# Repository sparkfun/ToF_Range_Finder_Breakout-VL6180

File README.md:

SparkFun ToF Range Finder Breakout - VL6180
===========================================

[*SparkFun ToF Range Finder Breakout - VL6180 (SEN-12784)*](https://www.sparkfun.com/products/12784)

This is a breakout board for the VL6180 Baby Bear time of flight range finder.
The VL6180 is actually a 3-in-1 package that combines an IR emitter, a range sensor, and an ambient light sensor together for you to easily use. 

Repository Contents
-------------------
* **/Hardware** - All Eagle design files (.brd, .sch)
* **/Libraries** - All Arduino libraries and board examples
* **/Production** - Test bed files and production panel files

Documentation
--------------
* **[Library](https://github.com/sparkfun/SparkFun_ToF_Range_Finder-VL6180_Arduino_Library)** - Arduino  library for the VL6180.
* **[Hookup Guide](https://learn.sparkfun.com/tutorials/vl6180-hookup-guide)** - Basic hookup guide for the VL6180.
* **[SparkFun Fritzing repo](https://github.com/sparkfun/Fritzing_Parts)** - Fritzing diagrams for SparkFun products.
* **[SparkFun 3D Model repo](https://github.com/sparkfun/3D_Models)** - 3D models of SparkFun products. 

License Information
-------------------
This product is _**open source**_! 

The **hardware** is released under [Creative Commons ShareAlike 4.0 International](https://creativecommons.org/licenses/by-sa/4.0/).

The **code** is beerware; if you see me (or any other SparkFun employee) at the local, and you've found our code helpful, please buy us a round!

Please use, reuse, and modify these files as you see fit. Please maintain attribution to SparkFun Electronics and release anything derivative under the same license.

Distributed as-is; no warranty is given.

- Your friends at SparkFun.

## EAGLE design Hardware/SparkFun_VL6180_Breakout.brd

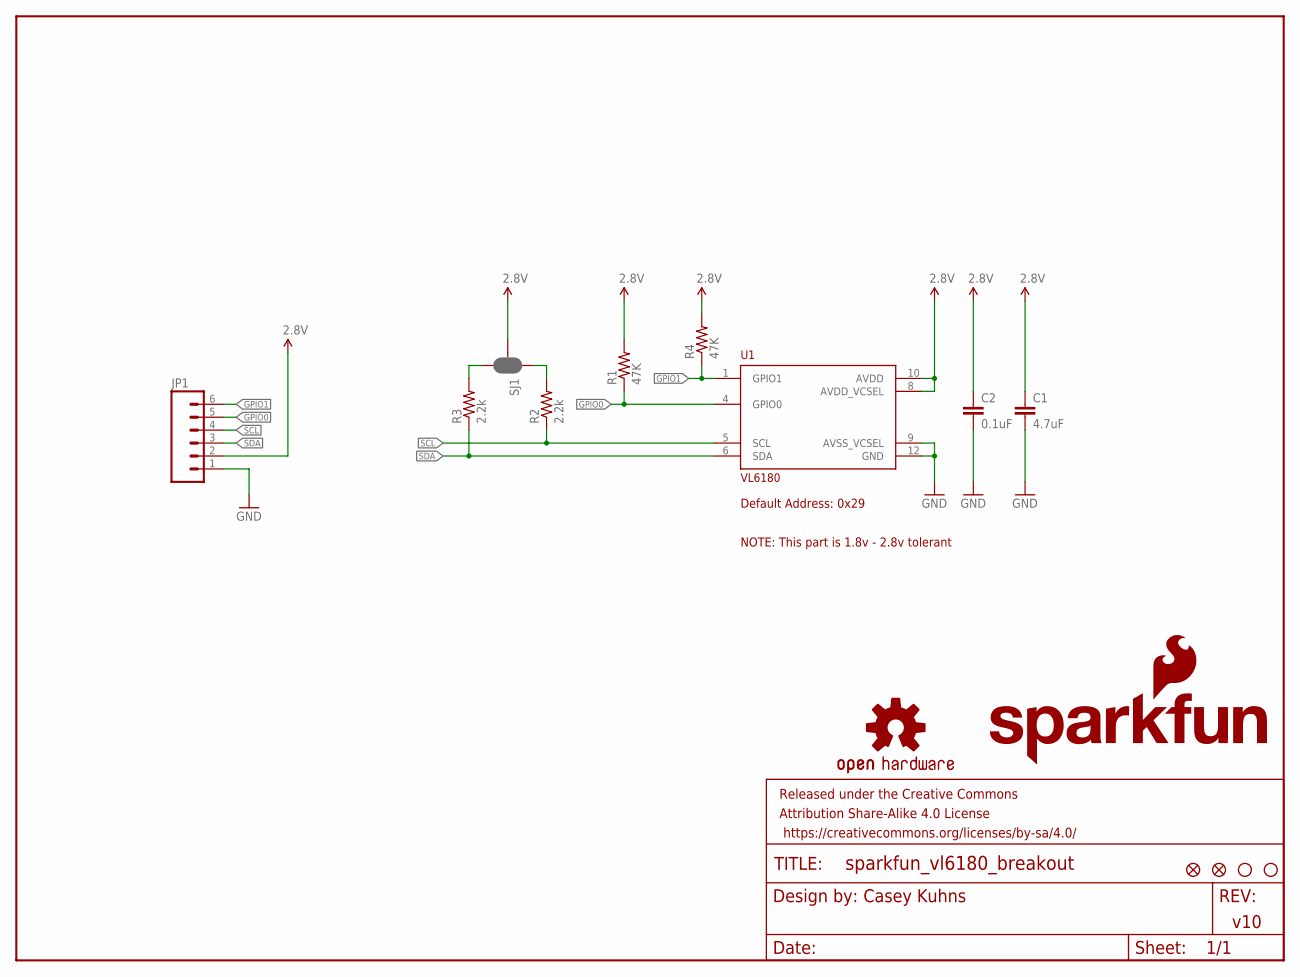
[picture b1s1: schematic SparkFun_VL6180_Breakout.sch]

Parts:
C1: 4.7uF; 0603-CAP
C2: 0.1uF; 0603-CAP
FID1, FID2: FIDUCIAL1X2; FIDUCIAL-1X2
FRAME1: FRAME-LETTER; CREATIVE_COMMONS
JP1: M06SIP; 1X06
LOGO1: SFE_LOGO_NAME_FLAME.1_INCH; SFE_LOGO_NAME_FLAME_.1
LOGO2: OSHW-LOGOS; OSHW-LOGO-S
R1, R4: 47K; 0603-RES
R2, R3: 2.2k; 0603-RES
SJ1: JUMPER-PAD-3-NC_BY_PASTE; PAD-JUMPER-3-NC_BY_PASTE_YES_SILK_FULL_BOX
STANDOFF1, STANDOFF2: STAND-OFF
U1: VL6180

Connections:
2.8V: C1.1, C2.1, JP1.2, R1.2, R4.2, SJ1.2, U1.8 (AVDD_VCSEL), U1.10 (AVDD)
GND: C1.2, C2.2, JP1.1, U1.9 (AVSS_VCSEL), U1.12 (GND)
GPIO0: JP1.5, R1.1, U1.4 (GPIO0)
GPIO1: JP1.6, R4.1, U1.1 (GPIO1)
unnamed: R2.2, SJ1.1
unnamed: R3.2, SJ1.3
SCL: JP1.4, R2.1, U1.5 (SCL)
SDA: JP1.3, R3.1, U1.6 (SDA)

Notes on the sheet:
Casey Kuhns
v10
Default Address: 0x29
NOTE: This part is 1.8v - 2.8v tolerant

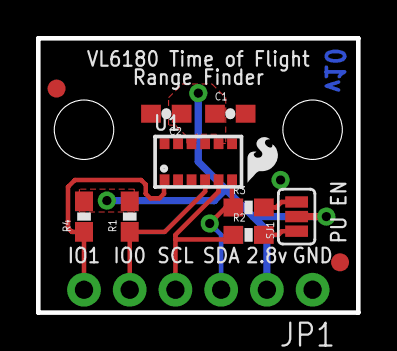
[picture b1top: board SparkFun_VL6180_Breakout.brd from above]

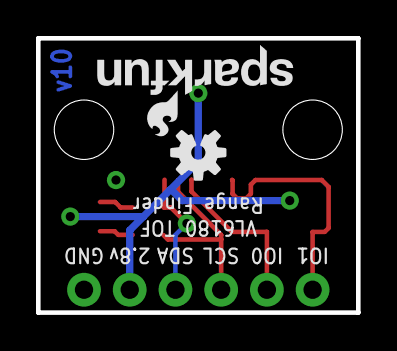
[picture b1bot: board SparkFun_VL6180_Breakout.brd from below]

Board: 2 copper layers, 17.8 x 15.2 mm, 17 parts (2 on the bottom side), 8 nets.

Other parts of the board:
U$2: SFE_LOGO_FLAME_.1

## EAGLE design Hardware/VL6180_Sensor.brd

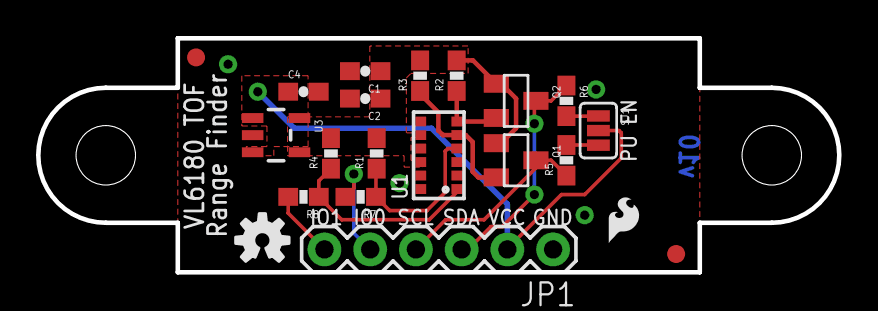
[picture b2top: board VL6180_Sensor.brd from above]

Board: 2 copper layers, 44.5 x 13.0 mm, 25 parts (1 on the bottom side), 13 nets.

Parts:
C1: 4.7uF; 0603-CAP
C2, C4: 0.1uF; 0603-CAP
FID1, FID2: FIDUCIAL1X2; FIDUCIAL-1X2
FRAME1: FRAME-LETTER; CREATIVE_COMMONS
JP1: 1X06
LOGO1: SFE_LOGO_NAME_FLAME.1_INCH; SFE_LOGO_NAME_FLAME_.1
LOGO2: OSHW-LOGOS; OSHW-LOGO-S
Q1, Q2: BSS138; SOT23
R1, R4: 47k; 0603-RES
R2, R3, R5, R6: 2.2k; 0603-RES
R7, R8: 10k; 0603-RES
SJ1: PAD-JUMPER-3-NC_BY_PASTE_YES_SILK_FULL_BOX
STANDOFF1, STANDOFF2: STAND-OFF
U1: VL6180
U3: MIC5219 3.3V; SOT23-5
U$2: SFE_LOGO_FLAME_.1

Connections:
2.8V: C1.1, C2.1, Q1.1, Q2.1, R1.2, R2.2, R3.2, R4.2, U1.8, U1.10, U3.5
GND: C1.2, C2.2, C4.2, JP1.1, U1.9, U1.12, U3.2
GPIO0: JP1.5, R7.2
GPIO1: JP1.6, R8.2
unnamed: R6.2, SJ1.1
unnamed: R5.2, SJ1.3
unnamed: R1.1, R7.1, U1.4
unnamed: R4.1, R8.1, U1.1
SCL: JP1.4, Q1.3, R5.1
SCL_LV: Q1.2, R3.1, U1.5
SDA: JP1.3, Q2.3, R6.1
SDA_LV: Q2.2, R2.1, U1.6
VCC: C4.1, JP1.2, SJ1.2, U3.1, U3.3

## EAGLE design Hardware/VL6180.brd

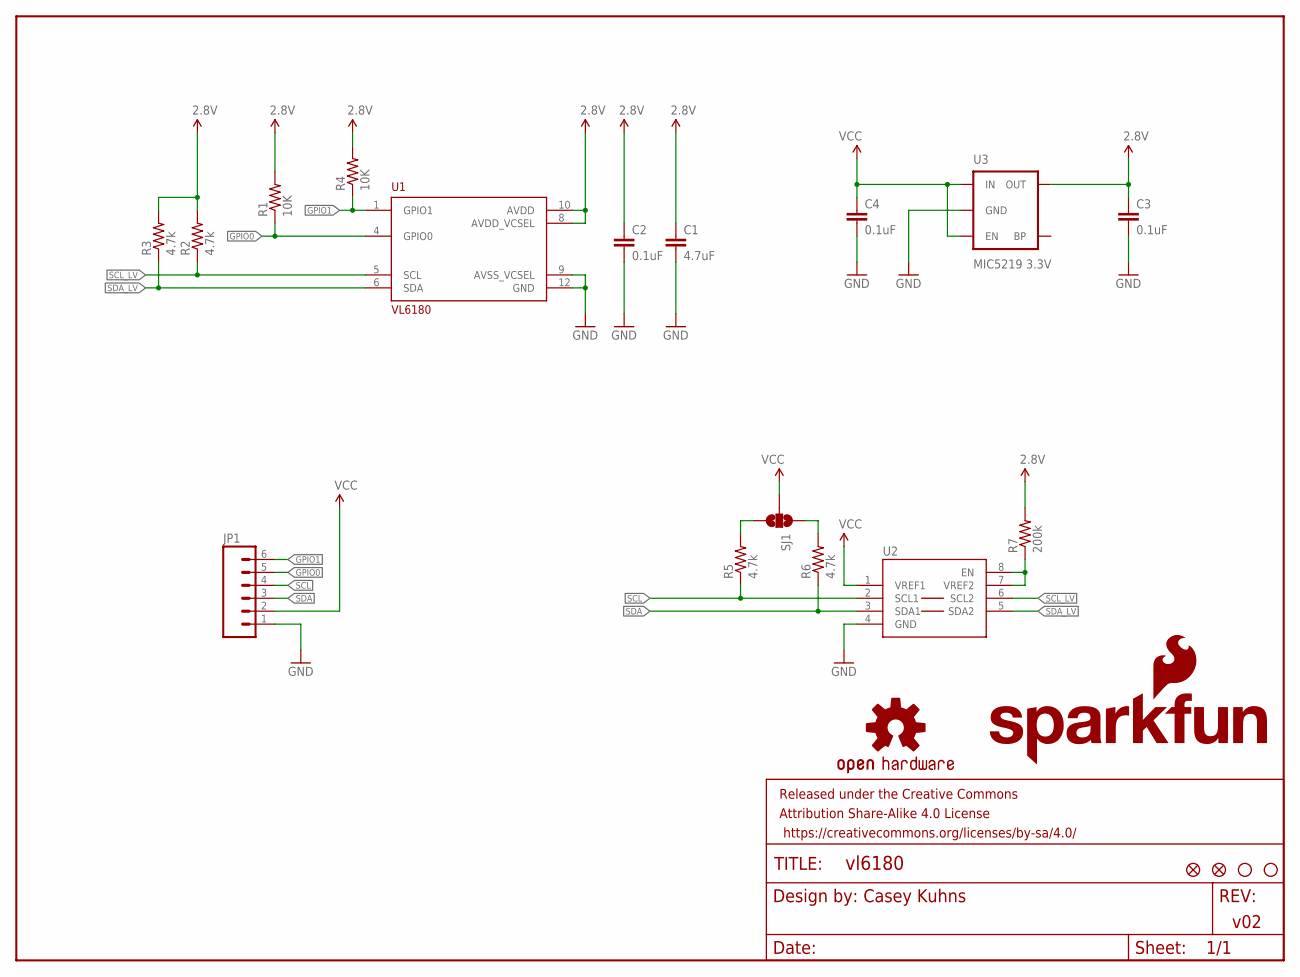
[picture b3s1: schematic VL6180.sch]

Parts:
C1: 4.7uF; 0603-CAP
C2, C3, C4: 0.1uF; 0603-CAP
FID1, FID2: FIDUCIAL1X2; FIDUCIAL-1X2
FRAME1: FRAME-LETTER; CREATIVE_COMMONS
JP1: M06SIP; 1X06
LOGO1: SFE_LOGO_NAME_FLAME.1_INCH; SFE_LOGO_NAME_FLAME_.1
LOGO2: OSHW-LOGOS; OSHW-LOGO-S
R1, R4: 10K; 0603-RES
R2, R3, R5, R6: 4.7k; 0603
R7: 200k; 0603-RES
SJ1: SOLDERJUMPER_2WAYPASTE1&2&3; SJ_3_PASTE1&2&3
STANDOFF1, STANDOFF2: STAND-OFF
U1: VL6180
U2: PCA9306; PSOP-8
U3: MIC5219 3.3V; SOT23-5

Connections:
2.8V: C1.1, C2.1, C3.1, R1.2, R2.2, R3.2, R4.2, R7.2, U1.8 (AVDD_VCSEL), U1.10 (AVDD), U3.5 (OUT)
GND: C1.2, C2.2, C3.2, C4.2, JP1.1, U1.9 (AVSS_VCSEL), U1.12 (GND), U2.4 (GND), U3.2 (GND)
GPIO0: JP1.5, R1.1, U1.4 (GPIO0)
GPIO1: JP1.6, R4.1, U1.1 (GPIO1)
unnamed: R7.1, U2.7 (VREF2), U2.8 (EN)
unnamed: R6.2, SJ1.1
unnamed: R5.2, SJ1.3
SCL: JP1.4, R5.1, U2.2 (SCL1)
SCL_LV: R2.1, U1.5 (SCL), U2.6 (SCL2)
SDA: JP1.3, R6.1, U2.3 (SDA1)
SDA_LV: R3.1, U1.6 (SDA), U2.5 (SDA2)
VCC: C4.1, JP1.2, SJ1.2, U2.1 (VREF1), U3.1 (IN), U3.3 (EN)

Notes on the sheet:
Casey Kuhns
v02

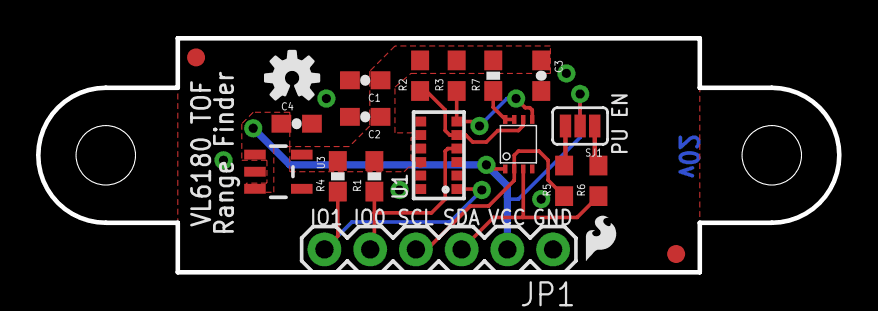
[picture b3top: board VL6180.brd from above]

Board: 2 copper layers, 44.5 x 13.0 mm, 24 parts (1 on the bottom side), 12 nets.

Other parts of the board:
U$2: SFE_LOGO_FLAME_.1

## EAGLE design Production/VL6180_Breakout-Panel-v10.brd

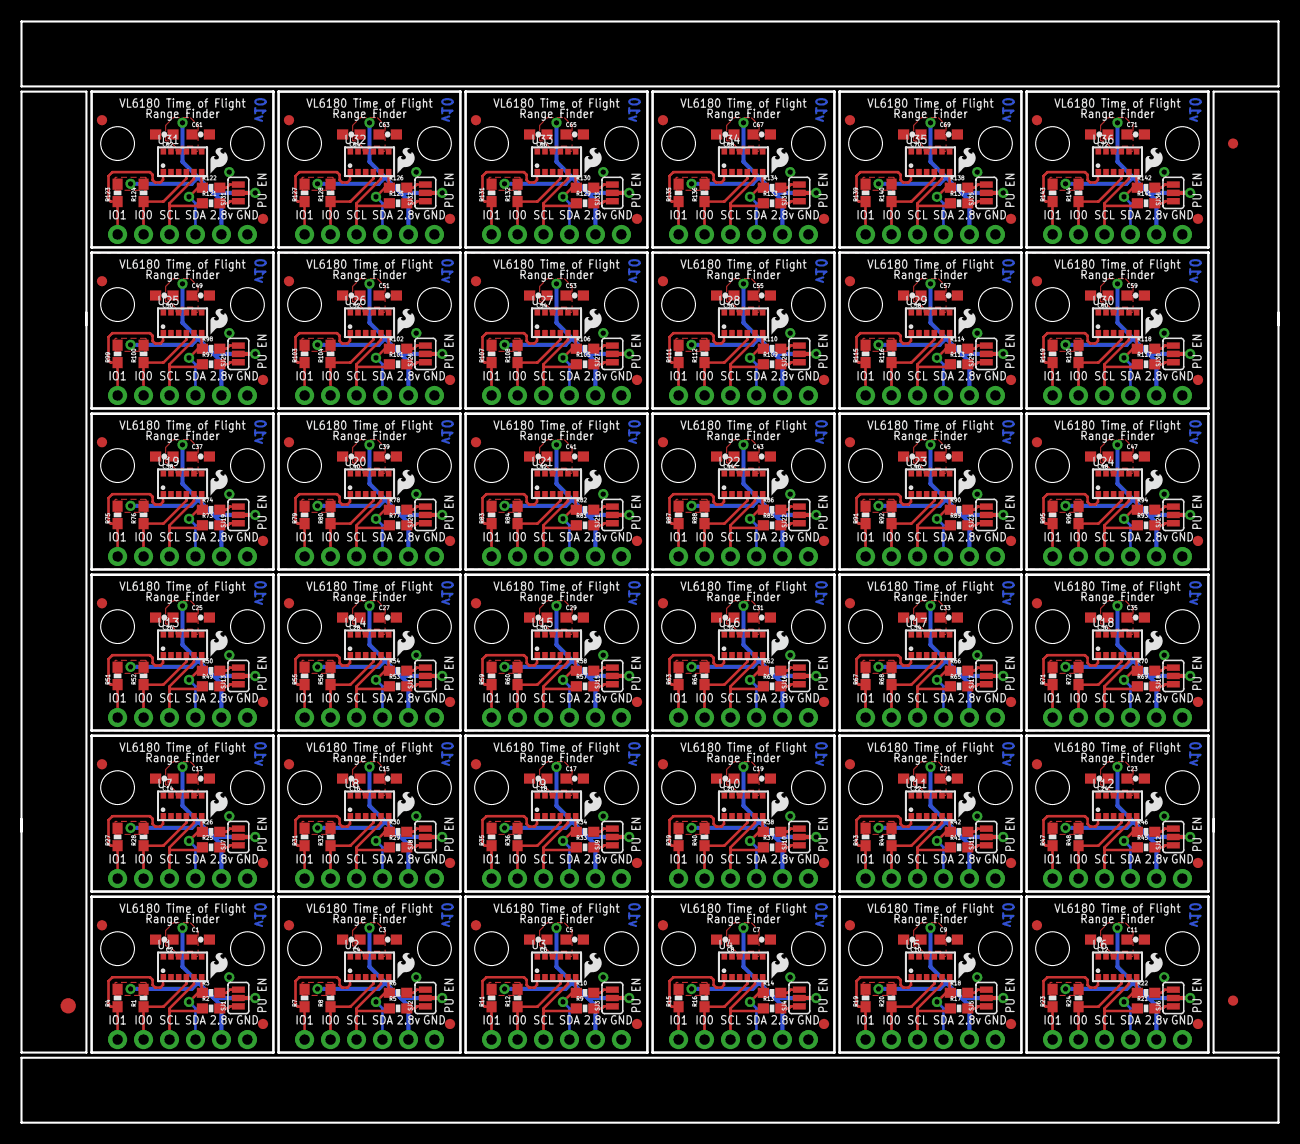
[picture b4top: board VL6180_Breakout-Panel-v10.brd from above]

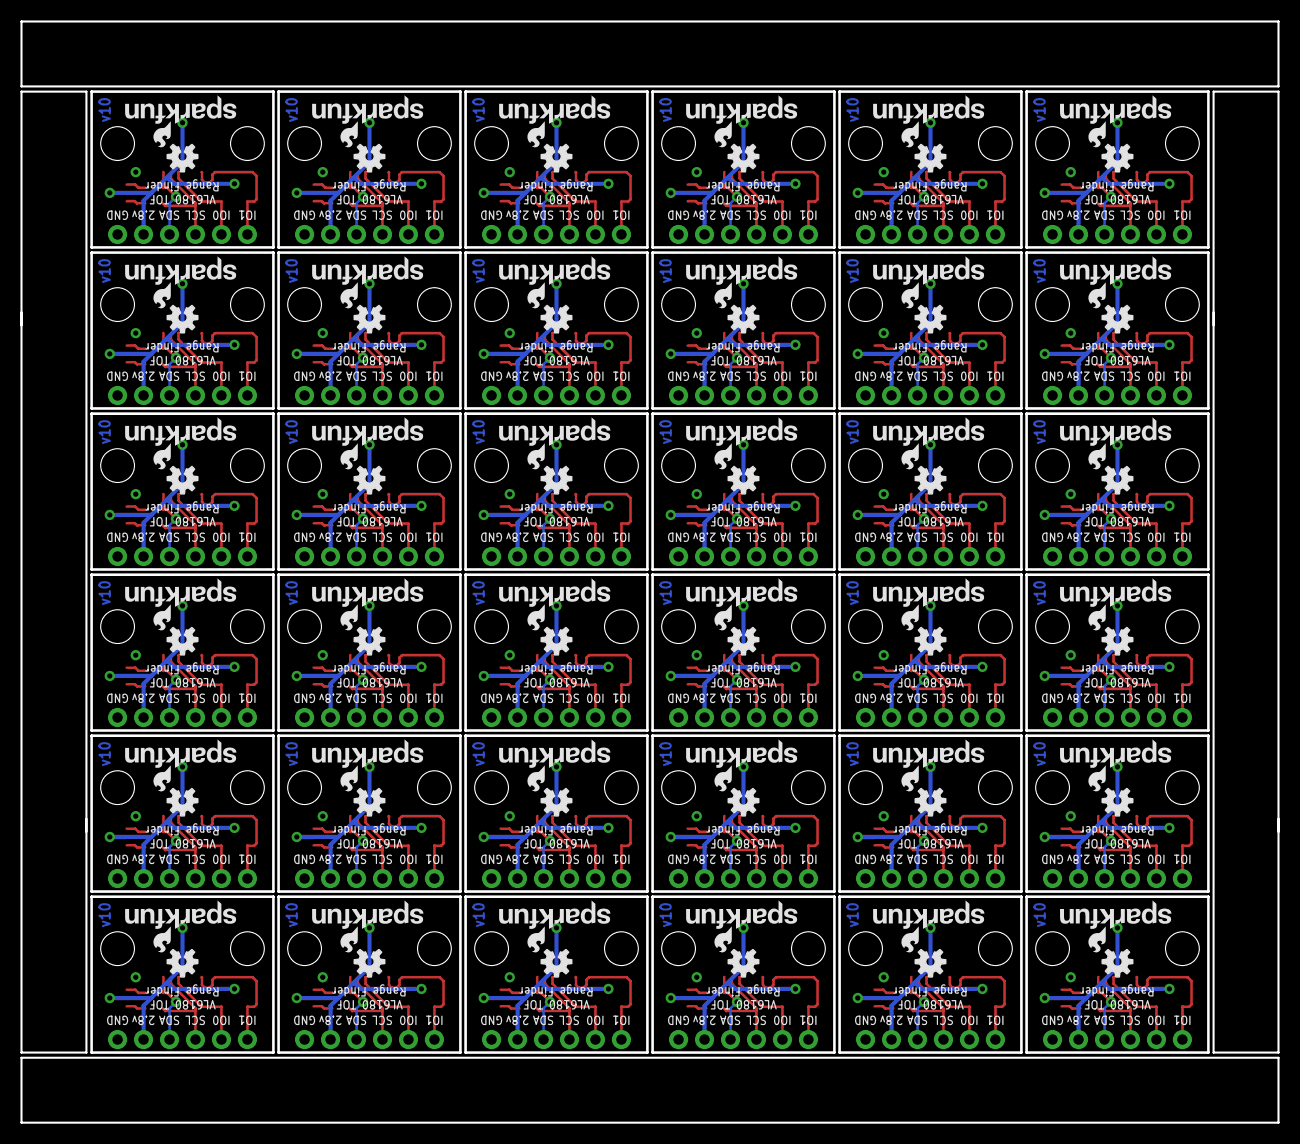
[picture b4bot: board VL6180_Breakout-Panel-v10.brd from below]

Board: 2 copper layers, 122.9 x 107.6 mm, 579 parts (72 on the bottom side), 288 nets.

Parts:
C1, C3, C5, C7, C9, C11, C13, C15, C17, C19, C21, C23, C25, C27, C29, C31, C33, C35, C37, C39, C41, C43, C45, C47, C49, C51, C53, C55, C57, C59, C61, C63, C65, C67, C69, C71: 4.7uF; 0603-CAP
C2, C4, C6, C8, C10, C12, C14, C16, C18, C20, C22, C24, C26, C28, C30, C32, C34, C36, C38, C40, C42, C44, C46, C48, C50, C52, C54, C56, C58, C60, C62, C64, C66, C68, C70, C72: 0.1uF; 0603-CAP
E$1: FIDUCIAL-1.5X3
E$4, E$6: FIDUCIAL-1X2
FID1, FID2, FID3, FID4, FID5, FID6, FID7, FID8, FID9, FID10, FID11, FID12, FID13, FID14, FID15, FID16, FID17, FID18, FID19, FID20, FID21, FID22, FID23, FID24, FID25, FID26, FID27, FID28, FID29, FID30, FID31, FID32, FID33, FID34, FID35, FID36, FID37, FID38, FID39, FID40, FID41, FID42, FID43, FID44, FID45, FID46, FID47, FID48, FID49, FID50, FID51, FID52, FID53, FID54, FID55, FID56, FID57, FID58, FID59, FID60, FID61, FID62, FID63, FID64, FID65, FID66, FID67, FID68, FID69, FID70, FID71, FID72: FIDUCIAL1X2; FIDUCIAL-1X2
JP1, JP2, JP3, JP4, JP5, JP6, JP7, JP8, JP9, JP10, JP11, JP12, JP13, JP14, JP15, JP16, JP17, JP18, JP19, JP20, JP21, JP22, JP23, JP24, JP25, JP26, JP27, JP28, JP29, JP30, JP31, JP32, JP33, JP34, JP35, JP36: 1X06
LOGO1, LOGO3, LOGO5, LOGO7, LOGO9, LOGO11, LOGO13, LOGO15, LOGO17, LOGO19, LOGO21, LOGO23, LOGO25, LOGO27, LOGO29, LOGO31, LOGO33, LOGO35, LOGO37, LOGO39, LOGO41, LOGO43, LOGO45, LOGO47, LOGO49, LOGO51, LOGO53, LOGO55, LOGO57, LOGO59, LOGO61, LOGO63, LOGO65, LOGO67, LOGO69, LOGO71: SFE_LOGO_NAME_FLAME.1_INCH; SFE_LOGO_NAME_FLAME_.1
LOGO2, LOGO4, LOGO6, LOGO8, LOGO10, LOGO12, LOGO14, LOGO16, LOGO18, LOGO20, LOGO22, LOGO24, LOGO26, LOGO28, LOGO30, LOGO32, LOGO34, LOGO36, LOGO38, LOGO40, LOGO42, LOGO44, LOGO46, LOGO48, LOGO50, LOGO52, LOGO54, LOGO56, LOGO58, LOGO60, LOGO62, LOGO64, LOGO66, LOGO68, LOGO70, LOGO72: OSHW-LOGOS; OSHW-LOGO-S
R1, R4, R7, R8, R11, R12, R15, R16, R19, R20, R23, R24, R27, R28, R31, R32, R35, R36, R39, R40, R43, R44, R47, R48, R51, R52, R55, R56, R59, R60, R63, R64, R67, R68, R71, R72, R75, R76, R79, R80, R83, R84, R87, R88, R91, R92, R95, R96, R99, R100, R103, R104, R107, R108, R111, R112, R115, R116, R119, R120, R123, R124, R127, R128, R131, R132, R135, R136, R139, R140, R143, R144: 47K; 0603-RES
R2, R3, R5, R6, R9, R10, R13, R14, R17, R18, R21, R22, R25, R26, R29, R30, R33, R34, R37, R38, R41, R42, R45, R46, R49, R50, R53, R54, R57, R58, R61, R62, R65, R66, R69, R70, R73, R74, R77, R78, R81, R82, R85, R86, R89, R90, R93, R94, R97, R98, R101, R102, R105, R106, R109, R110, R113, R114, R117, R118, R121, R122, R125, R126, R129, R130, R133, R134, R137, R138, R141, R142: 2.2k; 0603-RES
SJ1, SJ2, SJ3, SJ4, SJ5, SJ6, SJ7, SJ8, SJ9, SJ10, SJ11, SJ12, SJ13, SJ14, SJ15, SJ16, SJ17, SJ18, SJ19, SJ20, SJ21, SJ22, SJ23, SJ24, SJ25, SJ26, SJ27, SJ28, SJ29, SJ30, SJ31, SJ32, SJ33, SJ34, SJ35, SJ36: PAD-JUMPER-3-NC_BY_PASTE_YES_SILK_FULL_BOX
STANDOFF1, STANDOFF2, STANDOFF3, STANDOFF4, STANDOFF5, STANDOFF6, STANDOFF7, STANDOFF8, STANDOFF9, STANDOFF10, STANDOFF11, STANDOFF12, STANDOFF13, STANDOFF14, STANDOFF15, STANDOFF16, STANDOFF17, STANDOFF18, STANDOFF19, STANDOFF20, STANDOFF21, STANDOFF22, STANDOFF23, STANDOFF24, STANDOFF25, STANDOFF26, STANDOFF27, STANDOFF28, STANDOFF29, STANDOFF30, STANDOFF31, STANDOFF32, STANDOFF33, STANDOFF34, STANDOFF35, STANDOFF36, STANDOFF37, STANDOFF38, STANDOFF39, STANDOFF40, STANDOFF41, STANDOFF42, STANDOFF43, STANDOFF44, STANDOFF45, STANDOFF46, STANDOFF47, STANDOFF48, STANDOFF49, STANDOFF50, STANDOFF51, STANDOFF52, STANDOFF53, STANDOFF54, STANDOFF55, STANDOFF56, STANDOFF57, STANDOFF58, STANDOFF59, STANDOFF60, STANDOFF61, STANDOFF62, STANDOFF63, STANDOFF64, STANDOFF65, STANDOFF66, STANDOFF67, STANDOFF68, STANDOFF69, STANDOFF70, STANDOFF71, STANDOFF72: STAND-OFF
U1, U2, U3, U4, U5, U6, U7, U8, U9, U10, U11, U12, U13, U14, U15, U16, U17, U18, U19, U20, U21, U22, U23, U24, U25, U26, U27, U28, U29, U30, U31, U32, U33, U34, U35, U36: VL6180
U$1, U$2, U$3, U$4, U$5, U$6, U$7, U$8, U$9, U$10, U$11, U$12, U$13, U$14, U$15, U$16, U$17, U$18, U$19, U$20, U$21, U$22, U$23, U$24, U$25, U$26, U$27, U$28, U$29, U$30, U$31, U$32, U$33, U$34, U$35, U$36: SFE_LOGO_FLAME_.1

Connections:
2.8V: C1.1, C2.1, JP1.2, R1.2, R4.2, SJ1.2, U1.8, U1.10
2.8V1: C3.1, C4.1, JP2.2, R7.2, R8.2, SJ2.2, U2.8, U2.10
2.8V2: C5.1, C6.1, JP3.2, R11.2, R12.2, SJ3.2, U3.8, U3.10
2.8V3: C7.1, C8.1, JP4.2, R15.2, R16.2, SJ4.2, U4.8, U4.10
2.8V4: C9.1, C10.1, JP5.2, R19.2, R20.2, SJ5.2, U5.8, U5.10
2.8V5: C11.1, C12.1, JP6.2, R23.2, R24.2, SJ6.2, U6.8, U6.10
2.8V6: C13.1, C14.1, JP7.2, R27.2, R28.2, SJ7.2, U7.8, U7.10
2.8V7: C15.1, C16.1, JP8.2, R31.2, R32.2, SJ8.2, U8.8, U8.10
2.8V8: C17.1, C18.1, JP9.2, R35.2, R36.2, SJ9.2, U9.8, U9.10
2.8V9: C19.1, C20.1, JP10.2, R39.2, R40.2, SJ10.2, U10.8, U10.10
2.8V10: C21.1, C22.1, JP11.2, R43.2, R44.2, SJ11.2, U11.8, U11.10
2.8V11: C23.1, C24.1, JP12.2, R47.2, R48.2, SJ12.2, U12.8, U12.10
2.8V12: C25.1, C26.1, JP13.2, R51.2, R52.2, SJ13.2, U13.8, U13.10
2.8V13: C27.1, C28.1, JP14.2, R55.2, R56.2, SJ14.2, U14.8, U14.10
2.8V14: C29.1, C30.1, JP15.2, R59.2, R60.2, SJ15.2, U15.8, U15.10
2.8V15: C31.1, C32.1, JP16.2, R63.2, R64.2, SJ16.2, U16.8, U16.10
2.8V16: C33.1, C34.1, JP17.2, R67.2, R68.2, SJ17.2, U17.8, U17.10
2.8V17: C35.1, C36.1, JP18.2, R71.2, R72.2, SJ18.2, U18.8, U18.10
2.8V18: C37.1, C38.1, JP19.2, R75.2, R76.2, SJ19.2, U19.8, U19.10
2.8V19: C39.1, C40.1, JP20.2, R79.2, R80.2, SJ20.2, U20.8, U20.10
2.8V20: C41.1, C42.1, JP21.2, R83.2, R84.2, SJ21.2, U21.8, U21.10
2.8V21: C43.1, C44.1, JP22.2, R87.2, R88.2, SJ22.2, U22.8, U22.10
2.8V22: C45.1, C46.1, JP23.2, R91.2, R92.2, SJ23.2, U23.8, U23.10
2.8V23: C47.1, C48.1, JP24.2, R95.2, R96.2, SJ24.2, U24.8, U24.10
2.8V24: C49.1, C50.1, JP25.2, R99.2, R100.2, SJ25.2, U25.8, U25.10
2.8V25: C51.1, C52.1, JP26.2, R103.2, R104.2, SJ26.2, U26.8, U26.10
2.8V26: C53.1, C54.1, JP27.2, R107.2, R108.2, SJ27.2, U27.8, U27.10
2.8V27: C55.1, C56.1, JP28.2, R111.2, R112.2, SJ28.2, U28.8, U28.10
2.8V28: C57.1, C58.1, JP29.2, R115.2, R116.2, SJ29.2, U29.8, U29.10
2.8V29: C59.1, C60.1, JP30.2, R119.2, R120.2, SJ30.2, U30.8, U30.10
2.8V30: C61.1, C62.1, JP31.2, R123.2, R124.2, SJ31.2, U31.8, U31.10
2.8V31: C63.1, C64.1, JP32.2, R127.2, R128.2, SJ32.2, U32.8, U32.10
2.8V32: C65.1, C66.1, JP33.2, R131.2, R132.2, SJ33.2, U33.8, U33.10
2.8V33: C67.1, C68.1, JP34.2, R135.2, R136.2, SJ34.2, U34.8, U34.10
2.8V34: C69.1, C70.1, JP35.2, R139.2, R140.2, SJ35.2, U35.8, U35.10
2.8V35: C71.1, C72.1, JP36.2, R143.2, R144.2, SJ36.2, U36.8, U36.10
GND: C1.2, C2.2, JP1.1, U1.9, U1.12
GND1: C3.2, C4.2, JP2.1, U2.9, U2.12
GND2: C5.2, C6.2, JP3.1, U3.9, U3.12
GND3: C7.2, C8.2, JP4.1, U4.9, U4.12
GND4: C9.2, C10.2, JP5.1, U5.9, U5.12
GND5: C11.2, C12.2, JP6.1, U6.9, U6.12
GND6: C13.2, C14.2, JP7.1, U7.9, U7.12
GND7: C15.2, C16.2, JP8.1, U8.9, U8.12
GND8: C17.2, C18.2, JP9.1, U9.9, U9.12
GND9: C19.2, C20.2, JP10.1, U10.9, U10.12
GND10: C21.2, C22.2, JP11.1, U11.9, U11.12
GND11: C23.2, C24.2, JP12.1, U12.9, U12.12
GND12: C25.2, C26.2, JP13.1, U13.9, U13.12
GND13: C27.2, C28.2, JP14.1, U14.9, U14.12
GND14: C29.2, C30.2, JP15.1, U15.9, U15.12
GND15: C31.2, C32.2, JP16.1, U16.9, U16.12
GND16: C33.2, C34.2, JP17.1, U17.9, U17.12
GND17: C35.2, C36.2, JP18.1, U18.9, U18.12
GND18: C37.2, C38.2, JP19.1, U19.9, U19.12
GND19: C39.2, C40.2, JP20.1, U20.9, U20.12
GND20: C41.2, C42.2, JP21.1, U21.9, U21.12
GND21: C43.2, C44.2, JP22.1, U22.9, U22.12
GND22: C45.2, C46.2, JP23.1, U23.9, U23.12
GND23: C47.2, C48.2, JP24.1, U24.9, U24.12
GND24: C49.2, C50.2, JP25.1, U25.9, U25.12
GND25: C51.2, C52.2, JP26.1, U26.9, U26.12
GND26: C53.2, C54.2, JP27.1, U27.9, U27.12
GND27: C55.2, C56.2, JP28.1, U28.9, U28.12
GND28: C57.2, C58.2, JP29.1, U29.9, U29.12
GND29: C59.2, C60.2, JP30.1, U30.9, U30.12
GND30: C61.2, C62.2, JP31.1, U31.9, U31.12
GND31: C63.2, C64.2, JP32.1, U32.9, U32.12
GND32: C65.2, C66.2, JP33.1, U33.9, U33.12
GND33: C67.2, C68.2, JP34.1, U34.9, U34.12
GND34: C69.2, C70.2, JP35.1, U35.9, U35.12
GND35: C71.2, C72.2, JP36.1, U36.9, U36.12
GPIO0: JP1.5, R1.1, U1.4
GPIO1: JP1.6, R4.1, U1.1
GPIO2: JP2.5, R8.1, U2.4
GPIO3: JP2.6, R7.1, U2.1
GPIO4: JP3.5, R12.1, U3.4
GPIO5: JP3.6, R11.1, U3.1
GPIO6: JP4.5, R16.1, U4.4
GPIO7: JP4.6, R15.1, U4.1
GPIO8: JP5.5, R20.1, U5.4
GPIO9: JP5.6, R19.1, U5.1
GPIO10: JP6.5, R24.1, U6.4
GPIO11: JP6.6, R23.1, U6.1
GPIO12: JP7.5, R28.1, U7.4
GPIO13: JP7.6, R27.1, U7.1
GPIO14: JP8.5, R32.1, U8.4
GPIO15: JP8.6, R31.1, U8.1
GPIO16: JP9.5, R36.1, U9.4
GPIO17: JP9.6, R35.1, U9.1
GPIO18: JP10.5, R40.1, U10.4
GPIO19: JP10.6, R39.1, U10.1
GPIO20: JP11.5, R44.1, U11.4
GPIO21: JP11.6, R43.1, U11.1
GPIO22: JP12.5, R48.1, U12.4
GPIO23: JP12.6, R47.1, U12.1
GPIO24: JP13.5, R52.1, U13.4
GPIO25: JP13.6, R51.1, U13.1
GPIO26: JP14.5, R56.1, U14.4
GPIO27: JP14.6, R55.1, U14.1
GPIO28: JP15.5, R60.1, U15.4
GPIO29: JP15.6, R59.1, U15.1
GPIO30: JP16.5, R64.1, U16.4
GPIO31: JP16.6, R63.1, U16.1
GPIO32: JP17.5, R68.1, U17.4
GPIO33: JP17.6, R67.1, U17.1
GPIO34: JP18.5, R72.1, U18.4
GPIO35: JP18.6, R71.1, U18.1
GPIO36: JP19.5, R76.1, U19.4
GPIO37: JP19.6, R75.1, U19.1
GPIO38: JP20.5, R80.1, U20.4
GPIO39: JP20.6, R79.1, U20.1
GPIO40: JP21.5, R84.1, U21.4
GPIO41: JP21.6, R83.1, U21.1
GPIO42: JP22.5, R88.1, U22.4
GPIO43: JP22.6, R87.1, U22.1
GPIO44: JP23.5, R92.1, U23.4
GPIO45: JP23.6, R91.1, U23.1
GPIO46: JP24.5, R96.1, U24.4
GPIO47: JP24.6, R95.1, U24.1
GPIO48: JP25.5, R100.1, U25.4
GPIO49: JP25.6, R99.1, U25.1
GPIO50: JP26.5, R104.1, U26.4
GPIO51: JP26.6, R103.1, U26.1
GPIO52: JP27.5, R108.1, U27.4
GPIO53: JP27.6, R107.1, U27.1
GPIO54: JP28.5, R112.1, U28.4
GPIO55: JP28.6, R111.1, U28.1
GPIO56: JP29.5, R116.1, U29.4
GPIO57: JP29.6, R115.1, U29.1
GPIO58: JP30.5, R120.1, U30.4
GPIO59: JP30.6, R119.1, U30.1
GPIO60: JP31.5, R124.1, U31.4
GPIO61: JP31.6, R123.1, U31.1
GPIO62: JP32.5, R128.1, U32.4
GPIO63: JP32.6, R127.1, U32.1
GPIO64: JP33.5, R132.1, U33.4
GPIO65: JP33.6, R131.1, U33.1
GPIO66: JP34.5, R136.1, U34.4
GPIO67: JP34.6, R135.1, U34.1
GPIO68: JP35.5, R140.1, U35.4
GPIO69: JP35.6, R139.1, U35.1
GPIO70: JP36.5, R144.1, U36.4
GPIO71: JP36.6, R143.1, U36.1
unnamed: R2.2, SJ1.1
unnamed: R3.2, SJ1.3
unnamed: R5.2, SJ2.1
unnamed: R6.2, SJ2.3
unnamed: R9.2, SJ3.1
unnamed: R10.2, SJ3.3
unnamed: R13.2, SJ4.1
unnamed: R14.2, SJ4.3
unnamed: R17.2, SJ5.1
unnamed: R18.2, SJ5.3
unnamed: R21.2, SJ6.1
unnamed: R22.2, SJ6.3
unnamed: R25.2, SJ7.1
unnamed: R26.2, SJ7.3
unnamed: R29.2, SJ8.1
unnamed: R30.2, SJ8.3
unnamed: R33.2, SJ9.1
unnamed: R34.2, SJ9.3
unnamed: R37.2, SJ10.1
unnamed: R38.2, SJ10.3
unnamed: R41.2, SJ11.1
unnamed: R42.2, SJ11.3
unnamed: R45.2, SJ12.1
unnamed: R46.2, SJ12.3
unnamed: R49.2, SJ13.1
unnamed: R50.2, SJ13.3
unnamed: R53.2, SJ14.1
unnamed: R54.2, SJ14.3
unnamed: R57.2, SJ15.1
unnamed: R58.2, SJ15.3
unnamed: R61.2, SJ16.1
unnamed: R62.2, SJ16.3
unnamed: R65.2, SJ17.1
unnamed: R66.2, SJ17.3
unnamed: R69.2, SJ18.1
unnamed: R70.2, SJ18.3
unnamed: R73.2, SJ19.1
unnamed: R74.2, SJ19.3
unnamed: R77.2, SJ20.1
unnamed: R78.2, SJ20.3
unnamed: R81.2, SJ21.1
unnamed: R82.2, SJ21.3
unnamed: R85.2, SJ22.1
unnamed: R86.2, SJ22.3
unnamed: R89.2, SJ23.1
unnamed: R90.2, SJ23.3
unnamed: R93.2, SJ24.1
unnamed: R94.2, SJ24.3
unnamed: R97.2, SJ25.1
unnamed: R98.2, SJ25.3
unnamed: R101.2, SJ26.1
unnamed: R102.2, SJ26.3
unnamed: R105.2, SJ27.1
unnamed: R106.2, SJ27.3
unnamed: R109.2, SJ28.1
unnamed: R110.2, SJ28.3
unnamed: R113.2, SJ29.1
unnamed: R114.2, SJ29.3
unnamed: R117.2, SJ30.1
unnamed: R118.2, SJ30.3
unnamed: R121.2, SJ31.1
unnamed: R122.2, SJ31.3
unnamed: R125.2, SJ32.1
unnamed: R126.2, SJ32.3
unnamed: R129.2, SJ33.1
unnamed: R130.2, SJ33.3
unnamed: R133.2, SJ34.1
unnamed: R134.2, SJ34.3
unnamed: R137.2, SJ35.1
unnamed: R138.2, SJ35.3
unnamed: R141.2, SJ36.1
unnamed: R142.2, SJ36.3
SCL: JP1.4, R2.1, U1.5
SCL1: JP2.4, R5.1, U2.5
SCL2: JP3.4, R9.1, U3.5
SCL3: JP4.4, R13.1, U4.5
SCL4: JP5.4, R17.1, U5.5
SCL5: JP6.4, R21.1, U6.5
SCL6: JP7.4, R25.1, U7.5
SCL7: JP8.4, R29.1, U8.5
SCL8: JP9.4, R33.1, U9.5
SCL9: JP10.4, R37.1, U10.5
SCL10: JP11.4, R41.1, U11.5
SCL11: JP12.4, R45.1, U12.5
SCL12: JP13.4, R49.1, U13.5
SCL13: JP14.4, R53.1, U14.5
SCL14: JP15.4, R57.1, U15.5
SCL15: JP16.4, R61.1, U16.5
SCL16: JP17.4, R65.1, U17.5
SCL17: JP18.4, R69.1, U18.5
SCL18: JP19.4, R73.1, U19.5
SCL19: JP20.4, R77.1, U20.5
SCL20: JP21.4, R81.1, U21.5
SCL21: JP22.4, R85.1, U22.5
SCL22: JP23.4, R89.1, U23.5
SCL23: JP24.4, R93.1, U24.5
SCL24: JP25.4, R97.1, U25.5
SCL25: JP26.4, R101.1, U26.5
SCL26: JP27.4, R105.1, U27.5
SCL27: JP28.4, R109.1, U28.5
SCL28: JP29.4, R113.1, U29.5
SCL29: JP30.4, R117.1, U30.5
SCL30: JP31.4, R121.1, U31.5
SCL31: JP32.4, R125.1, U32.5
SCL32: JP33.4, R129.1, U33.5
SCL33: JP34.4, R133.1, U34.5
SCL34: JP35.4, R137.1, U35.5
SCL35: JP36.4, R141.1, U36.5
SDA: JP1.3, R3.1, U1.6
SDA1: JP2.3, R6.1, U2.6
SDA2: JP3.3, R10.1, U3.6
SDA3: JP4.3, R14.1, U4.6
SDA4: JP5.3, R18.1, U5.6
SDA5: JP6.3, R22.1, U6.6
SDA6: JP7.3, R26.1, U7.6
SDA7: JP8.3, R30.1, U8.6
SDA8: JP9.3, R34.1, U9.6
SDA9: JP10.3, R38.1, U10.6
SDA10: JP11.3, R42.1, U11.6
SDA11: JP12.3, R46.1, U12.6
SDA12: JP13.3, R50.1, U13.6
SDA13: JP14.3, R54.1, U14.6
SDA14: JP15.3, R58.1, U15.6
SDA15: JP16.3, R62.1, U16.6
SDA16: JP17.3, R66.1, U17.6
SDA17: JP18.3, R70.1, U18.6
SDA18: JP19.3, R74.1, U19.6
SDA19: JP20.3, R78.1, U20.6
SDA20: JP21.3, R82.1, U21.6
SDA21: JP22.3, R86.1, U22.6
SDA22: JP23.3, R90.1, U23.6
SDA23: JP24.3, R94.1, U24.6
SDA24: JP25.3, R98.1, U25.6
SDA25: JP26.3, R102.1, U26.6
SDA26: JP27.3, R106.1, U27.6
SDA27: JP28.3, R110.1, U28.6
SDA28: JP29.3, R114.1, U29.6
SDA29: JP30.3, R118.1, U30.6
SDA30: JP31.3, R122.1, U31.6
SDA31: JP32.3, R126.1, U32.6
SDA32: JP33.3, R130.1, U33.6
SDA33: JP34.3, R134.1, U34.6
SDA34: JP35.3, R138.1, U35.6
SDA35: JP36.3, R142.1, U36.6

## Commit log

2014-02-21 initial commit with initial hardware layout
2014-02-28 Boad Layout finished, looking for review
2014-03-03 finished layout and added simple breakout board layout
2014-03-03 changed VCC label on breakout to 2.8v to re-state 2.8v compatible
2014-03-04 Changed I2C EN to PU EN
2014-03-13 fixed flipped pin problem. 8-9 on the sensor were reversed somehow. All better :)
2014-03-25 added pin 1 designator
2014-05-01 modified: Hardware/VL6180_Breakout.brd modified: Hardware/VL6180_Breakout.sch renamed: Hardware/VL6180.brd -> Hardware/VL6180_Sensor.brd renamed: Hardware/VL6180.sch -> Hardware/VL6180_Sensor.sch
    Removed I2C level shifter and switched to Fet bases solution.
    New solderpaste footprint for VL6180 for improved reflow.
    updated all parts with Sparkle ID's
2014-05-28 changed I2C resistors to 2.2k, added current limiting resistor on GPIO pins.
2014-05-29 moved wire to clear resistor better, re-oriented Silkscreen to match direction of logo.
2014-05-29 created Sensor panel v10
2014-05-29 created breakout panel v10
2014-10-28 started work on Library
2014-10-29 added files to libs
2014-10-29 worked on the class
2014-10-31 work in progress
2015-01-23 worked on Library, currently functioning, building more features
2015-02-10 split repo
2015-02-13 Updating README with product info
2015-05-14 Fixing structure, naming conventions
2015-05-14 Squashed 'Libraries/Arduino/' content from commit dd6cce0
    git-subtree-dir: Libraries/Arduino
    git-subtree-split: dd6cce03c074b9068238a3e29b15535ec5eadf2b

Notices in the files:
parts and their libraries:
SparkFun-Aesthetics: Licensing: CC v3.0 Share-Alike You are welcome to use this library for commercial purposes.
SparkFun-Aesthetics: Released under the Creative Commons Attribution Share-Alike 4.0 License
SparkFun-Aesthetics: Released under the Creative Commons
